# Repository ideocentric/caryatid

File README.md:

# caryatid

**A carrier board that gives a Daisy Seed a rechargeable battery, honest power
indication, and a fixed set of I/O on connectors, in a shape that drops into an
enclosure.**

Plenty of Seed carriers break out pins well. Fewer solve *running on a battery
you can charge without opening the box, and knowing what state that battery is
in when the instrument is switched off*. This board treats that as the core
requirement rather than an accessory.

**One PCB layout serves every build.** Every variable element (pots, keypad,
sensors, switches, comms) enters through a connector, and each instrument
populates the subset it needs. Order once, stuff per instrument. It carries
absonus, loa, baby borg, and whatever comes next.

### Is it right for what you are building?

**[docs/platform.md](docs/platform.md)** is the capability specification: what
it supports, what it deliberately does not, and where the boundary sits. It
states the limits as plainly as the features, because knowing them before you
commit is worth more than discovering them after.

### Status

**Five boards ordered 2026-08-23; none has been powered yet.**

Every electrical check is at zero: no unconnected nets, no shorts, no clearance
or hole violations, no copper under the width rule, no floating ground, and no
DRC violations of any kind. The firmware stub compiles against libDaisy and has
never been run on hardware. [docs/status.md](docs/status.md) is the current
state; treat anything marked unverified there as exactly that.

> **Working on caryatid itself rather than building with it?** Read
> [the checkout warning](#working-on-caryatid-itself) at the foot of this file
> before you commit anything. It is the one way to lose a session's work here.

## Start here

| | |
| --- | --- |
| **Where the board is, and what is next** | [docs/status.md](docs/status.md) |
| **The frozen pin map** | [docs/pinmap.md](docs/pinmap.md) — generated from [docs/pins.yaml](docs/pins.yaml) |
| Connectors and what plugs into them | [docs/connectors.md](docs/connectors.md) |
| Audio in and out, and the handset problem | [docs/audio.md](docs/audio.md) |
| **Setting the mic capsule jumpers** | [docs/mic-configurations.md](docs/mic-configurations.md) |
| The three indicators, and why three | [docs/indicators.md](docs/indicators.md) |
| **Component values, with derivations** | [docs/values.md](docs/values.md) |
| Part numbers, footprints, what is in stock | [docs/sourcing.md](docs/sourcing.md) |
| **Power sheet, every connection** | [docs/power-sheet.md](docs/power-sheet.md) |
| **Seed sheet, every connection** | [docs/seed-sheet.md](docs/seed-sheet.md) |
| **Panel I/O sheet, every connection** | [docs/panel-io-sheet.md](docs/panel-io-sheet.md) |
| **How to build an instrument on this board** | [docs/integration.md](docs/integration.md) |
| Board-support firmware (MIT) | [firmware/](firmware/) |
| What to do before and during capture | [docs/capture-checklist.md](docs/capture-checklist.md) |
| Datasheets, links and document numbers | [docs/datasheets.md](docs/datasheets.md) |
| **What it supports, and what it does not** | [docs/platform.md](docs/platform.md) |
| The board and schematic as PDFs | [docs/reference/](docs/reference/) |
| Why things are the way they are | [docs/decisions/](docs/decisions/) |
| **Rules the tools must follow, and what each cost** | [docs/conventions.md](docs/conventions.md) |

**`docs/pins.yaml` is the source of truth.** The markdown table is generated:

```sh
python3 tools/gen_pinmap.py           # rewrite docs/pinmap.md
python3 tools/gen_pinmap.py --check   # fail if stale
```

Never edit `pinmap.md` by hand. A pin map kept in two places will disagree the
first time a connector moves.

## Terms

**DNP — "do not populate."** The footprint is on the board, the symbol is in the
schematic, the connections exist in the netlist, but **no component is soldered
there**. A deliberately empty position. Also written DNI (do not install), NF
(not fitted), or NP.

**caryatid has none, and that is the point of the term appearing here.**
[ADR 0010](docs/decisions/0010-nothing-is-dnp.md) took the count to zero and
`check_board.py` check 12 keeps it there.

DNP used to be the mechanism this board rested on: lay out every option any of
the instruments might need, populate only the subset each build wants. It stopped
paying its way when JLCPCB began fitting the through-hole parts too — **DNP
became an instruction someone acts on and bills for**, so every DNP line is
either a part you paid for and did not want or one you needed and did not get,
and which it is only becomes clear when the boards arrive.

What replaced it is **selection after assembly**: six jumpers choose the mic
front-end per channel, and the codec's own PGA does the attenuating a resistor
pad used to. See [audio.md](docs/audio.md) and
[sourcing.md](docs/sourcing.md).

## What "frozen" means

An instrument may leave a pin unpopulated, and may choose between the alternates
listed for a pin. It may **not** repurpose one. The entire value of the platform
is that one layout serves every build; a pin reassigned for one instrument is a
board that no longer serves the others.

The map is **fully allocated**. `D30` is the only spare. Adding anything means
taking it from something else, and the decision records say what that would
cost.

## The fixed core

Populated on every build:

- Barrel jack → SS34 → **bq24074** charger with power path, ISET 890 Ω (1 A)
- **On-board 18650 holder (BT1)**, the only path to `VBAT` — a soldered holder
  cannot be wired backwards. Protected cell or protection PCB **required**
- **TPS61023** boost → **5.0 V** → ferrite + 100 µF → Seed VIN
- Illuminated latching power switch (3–9 V lamp, so `R_LED` is a 0 Ω link)
- `/CHG` + `/PGOOD` panel LEDs — the indication that works with the Seed off
- RGB status LED, battery gauge on A10, charge-status code on A11
- Daisy Seed on 2×(1×20) female headers, machine-fitted
- 74HC14 Schmitt debounce, SMT — see [ADR 0007](docs/decisions/0007-rc-and-schmitt-instead-of-the-ls18-p.md)
- Audio out; audio in on every board, **both channels**, capsule selected by
  jumper — JP1–JP3 left, JP4–JP6 right

## Two things worth knowing before you read the map

**Comms ports carry signals, not protocols.** D11/D12 are simultaneously I2C1
and UART4, so the same connector is an I2C sensor, a MIDI input, or an ESP32
bridge depending on what you plug in. Two ports is the ceiling — there is no
third UART on free pins. See [ADR 0003](docs/decisions/0003-comms-ports-are-protocol-agnostic.md).

**D8 is the only free SPI1 clock on the board.** Not a preference — `PA5` is the
only alternative and it is an analogue panel input. An earlier draft spent D8 on
an LED, which would have left SPI1 as two pins with nothing to clock them. See
[ADR 0004](docs/decisions/0004-keep-spi1-drop-the-soft-latch.md).

## Licence

**Settled 2026-08-18.** The hardware and the tools are strongly reciprocal; the
board-support layer deliberately is not:

| What | Licence |
| --- | --- |
| **Hardware** — schematics, PCB, footprints, artwork | **CERN-OHL-S v2** |
| **Tools** — everything in `tools/` | **GPL-3.0-or-later** |
| **Board support** — everything in `firmware/` | **MIT** |

Terms and what counts as *Complete Source* are in [LICENSING.md](LICENSING.md); how
it was reached, and the audit of every design input, are in
[ADR 0006](docs/decisions/0006-licensing-is-open.md).

CERN-OHL-S defines Complete Source as the **editable design files**, so shipping
Gerbers alone does not discharge the obligation. `CERN-OHL-S v2` and
`github.com/ideocentric/caryatid` are both printed on the front silkscreen.

The question this turned on — whether the schematic derived from Adafruit's
reference designs (CC BY-SA, and irreversible) or was drawn independently from
the TI datasheets — was answered **2026-08-08, before capture began**: drawn from
the datasheets. That is what kept the reciprocal option available.

**`firmware/` is MIT on purpose.** A copyleft board-support layer is viral into
anything that links it, which would settle every instrument's firmware licence
from underneath — a decision belonging to each instrument, not to the carrier
board. libDaisy and DaisySP are MIT already.

## Consuming this board

Each instrument takes it as a submodule:

```sh
git submodule add https://github.com/ideocentric/caryatid.git hardware/platform
```

loa consumes it this way at `hardware/platform`. Then add the board support to
your build:

```make
C_INCLUDES  += -Ihardware/platform/firmware/include
CPP_SOURCES += hardware/platform/firmware/src/caryatid.cpp
```

**Read [docs/integration.md](docs/integration.md) first** — it covers what the
board provides, what the instrument must provide, the electrical and mechanical
requirements, and the four things about this board that are not guessable from
a pin number.

## The name

*A caryatid is a column carved as a figure, bearing the weight of what stands on
it. Named for the role rather than for any instrument it carries: calling it
after one of them would have implied it belonged to that one.*

## Working on caryatid itself

### ⚠ Which checkout is this?

**caryatid is developed as a standalone clone. It is also consumed as a git
submodule by the instrument repositories, and those copies are read-only.**

If the path to this file runs through another project's submodule directory —
for loa that is `hardware/platform/` — **you are in a consumer copy. Do not edit
it and do not commit to it.** Find the standalone clone and work there.

The sequence, in order, every time:

1. Change, review and commit in the **standalone clone**.
2. Push.
3. *Then* update the consuming repository's submodule pointer — a
   `Bump caryatid: …` commit on that side.

**Why this matters more than it looks.** A submodule checkout sits on a detached
HEAD, so commits made there belong to no branch and the standalone clone knows
nothing about them. The two diverge silently, and the symptoms all point
somewhere other than the cause: KiCad in one directory keeps showing a schematic
that another directory has already changed.

That is not hypothetical. A whole session's work — ADR 0010, the schematic
edits, two tools, thirteen documents — was written into loa's submodule on
2026-08-21. It pushed to the same remote so nothing was lost, but an hour went
into diagnosing "update from schematic shows nothing new", which was only ever
the wrong directory.

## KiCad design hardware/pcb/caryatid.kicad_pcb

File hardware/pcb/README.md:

# PCB

KiCad 9 project. **All four sheets are captured.** 125 components, 101 nets,
**ERC clean at 0 violations.**

| Sheet | State | Check |
| --- | --- | --- |
| `power.kicad_sch` | 27 components, 19 nets | netlist diffed node-by-node against [power-sheet.md](../../docs/power-sheet.md); `ITERM` the one deliberate no-connect |
| `seed.kicad_sch` | 12 components | all **31** physical pins in `pins.yaml` land on a net named after the pin |
| `panel-io.kicad_sch` | 46 components | all **29** pins declaring a connector reach it, traversing series R and the debouncer |
| `audio.kicad_sch` | 37 placements, **0 DNP** | 17 nets diffed against [audio.md](../../docs/audio.md), including `C_g` in series with `R_g`; six jumpers re-diffed for [ADR 0010](../../docs/decisions/0010-nothing-is-dnp.md) |

**The dangling-global count reached zero.** It ran 33 → 4 → 0 as seed, panel-io
and audio landed, and each drop was predicted before the sheet was drawn. Five
no-connects remain and all five are deliberate: `ITERM` on the charger, `J11`
pin 9 (the spare), and the three unused 74HC14 outputs.

Treat any *new* ERC message as real. The design now has nothing expected to be
wrong, so there is no noise for a fault to hide in.

Placement is functional rather than tidy — components on a 1.27 mm grid with
labelled stubs, meant to be dragged into shape in the GUI. The bootstrap scripts
in [`tools/oneshot/`](../../tools/oneshot/) are spent; do not re-run them.

```
pcb/
  caryatid.kicad_pro       project: net classes, design rules, sheet index
  caryatid.kicad_sch       root — four hierarchical sheets, nothing else
  power.kicad_sch          charger, boost, latch, hardware charge LEDs
  seed.kicad_sch           Seed headers, battery gauge, charge-status code
  audio.kicad_sch          jacks, coupling, mic bias / preamp / pad options
  panel-io.kicad_sch       analogue bus, digital bus, switches, comms ports
  caryatid.kicad_sym       symbols: BQ24074RGT, TPS61023DRL, Seed sockets A/B
  caryatid.pretty/         footprints: BQ24074 QFN, Seed sockets A/B
  sym-lib-table            so the project libs resolve without global config
  fp-lib-table
```

Open `caryatid.kicad_pro`. `caryatid.kicad_pcb` carries **all 125 footprints,
placed and net-bound**, on a 150 × 90 mm outline with four M3 holes. **Nothing is
routed** — DRC's 263 unconnected items are the full ratsnest, which is correct.

Placement is a machine first pass, not layout. It puts each block where the
zoning says and nothing overhangs the outline, but ~33 courtyards still overlap
and the silkscreen is a mess. Treat it as something to drag from.

## Which face

**Everything is on the front.** The back carries nothing but the ground pour.

The SMD was briefly on the back, which is the textbook arrangement and was right
when the board was 90 × 100 and the copper under the cell was worth reclaiming.
It is wrong here: **the enclosure is shallow, so the standoff must be short**, and
C7 at 5.4 mm cannot hang underneath a 2 mm gap. Moving everything to the front
fixes three things at once — the standoff drops to 2 mm, SMT stays single-sided
and therefore Economic, and B.Cu is freed as a routing layer instead of carrying
104 parts *and* every signal.

The flip is stored the way KiCad stores it, checked against a KiCad-written
board rather than assumed: back-side footprints hold **Y-negated** coordinates,
F/B layer names swapped, and `(justify mirror)` on every text. Arcs survive
because KiCad 7+ stores start/mid/end and all three mirror together.

**Two things to confirm before ordering.**

`J13` is the SMD Qwiic socket, so it classified as SMD and went to the back.
Electrically fine; whether you want a Qwiic cable leaving from the underside is
a mechanical question, not one the classifier can answer.

**Through-hole bodies are on the front, so their pins protrude into the SMD
side.** JLC cannot wave-solder them from the back without hitting SMD. For small
runs their through-hole work is hand soldering, which is probably fine — but you
asked for the JSTs to be machine-fitted as on absonus, and absonus had a
component-free underside. Worth putting to JLC before the order.

## The connector ring

Placed by function, and stacked from measured courtyard extents rather than by
hand — hand arithmetic on offsets produced touching parts three times running.

| Edge | Connectors |
| --- | --- |
| Left | `J1` DC in, `J3` latch switch, `J4` charge LEDs |
| Left, inboard | `J11` digital bus IDC, beside A1 (the digital row) |
| Right | `J12` RGB, `J9` soft pot, `J10` FSR, `J17` audio out |
| Right, inboard | `J5` analogue bus IDC beside A2; `J16` expansion; `J18` audio in and `J14` mic return together |
| Bottom | `J6` `J7` `J8` switches, then `J19` and `J15` module ports |

Power enters on the left where the charger and boost sit underneath; the
analogue bus, both sensors and the audio pair are on the right, furthest from
L1. `J18` and `J14` are adjacent because they are one loom — capsule signal and
its bias return to the hook switch's second pole.

**Everything is at rotation 0.** A vertical JST exits upward, so turning the pin
row to follow the edge buys nothing — and the rotated-courtyard transform is the
one piece of geometry here that could not be checked against a known-good file,
so it is not used. If you rotate parts by hand in the GUI, KiCad does that
arithmetic correctly.

**The four M3 holes are part of the collision check.** They were not, at first,
and that version passed a board where `J6` and `J18` each sat on top of a
mounting hole. They come from the skeleton rather than from the netlist, which
is exactly why a check built around the component list missed them.

## Routing: the pour and the boost loop only

**Everything else is unrouted, deliberately.** kicad-cli has no router, KiCad
ships none, and Freerouting is not installed — and routing follows placement,
which is still a machine first pass. Two pieces were worth doing now because
their geometry is settled and the stakes are high.

**A GND zone on B.Cu**, which is now the empty face — a genuinely solid plane,
and the whole layer still available for routing around it.

**The zone is not filled.** `kicad-cli pcb drc` has no fill option, so DRC
reports the two GND vias as `via_dangling` — they touch a zone that has no copper
in it yet. **Fill zones in the board editor (`B`) and both clear.** That is a
tooling limit, not a fault.

**The boost hot loop.** `+5V_RAW` runs U2 pin 6 to C6 at 0.8 mm. The return is
deliberately **not a track**: C6's ground pad and U2's ground pad each drop a via
into the plane, so the return current runs directly beneath the outgoing current.
That is the smallest loop available and a track would be strictly worse.

Two things learned the hard way and worth keeping:

- **A track wider than the pad pitch shorts to the neighbouring pad.** 0.8 mm
  centred on U2 pin 6 overlapped pin 5. Every exit from a 0.5 mm-pitch pad now
  necks to 0.25 mm and widens once clear of the pad field.
- **Via positions are searched against every back-side pad**, not chosen by eye.
  The first attempt put a GND via straight through C7's `+5V` pad.

**`SW` is routed, and C6 moved to make it possible.** Putting the output cap
beside U2 was the obvious choice and it quietly cost the switching node: pin 5
can only exit right, and C6 was standing in that gap. C6 now sits **below** U2,
which frees the right side for L1 and — because pin 6 is on the near edge either
way — barely lengthens the hot loop.

| | beside | **below** |
| --- | --- | --- |
| Hot loop, pin 6 → C6 | 1.84 mm | 2.01 mm |
| SW node, pin 5 → L1 | 4.17 mm, **unroutable** | **2.31 mm at 1.2 mm wide** |

Trading 0.17 mm of hot loop for a routable 1.5 A switching node is not a close
call. The lesson is that *routability* is a placement constraint, and optimising
loop length without it produced an arrangement that measured well and could not
be built.

Three power pins leaving a 0.5 mm-pitch package share a 1.5 mm band, so every
exit necks to 0.2 mm and widens only once clear of the pad field. With that, the
routing adds **no** DRC violations of its own — the four clearance items are the
pre-existing SOT-563 pad-pitch ones.

## Routing the rest: Specctra DSN

`kicad-cli` has no router and no `dsn` export, so `tools/export_dsn.py` writes one:

```sh
python3 tools/export_dsn.py                 # -> hardware/pcb/caryatid.dsn
freerouting -de hardware/pcb/caryatid.dsn -do hardware/pcb/caryatid.ses
# KiCad: File > Import > Specctra Session
```

KiCad's own GUI export (File > Export > Specctra DSN) is more authoritative; this
exists so the export can be produced headlessly. The `.dsn` and `.ses` are
gitignored — regenerate rather than commit.

Two things it does that the GUI export does not:

- **GND is excluded from the routed nets.** F.Cu is a ground plane, which
  Freerouting cannot see, so it would otherwise scribble 72 ground traces across
  the board. GND wants stitching vias instead. `--with-gnd` overrides.
- **Existing copper is emitted `(type protect)`.** The boost hot loop and the SW
  node were placed and measured by hand; this stops the router discarding them.

**Not verified against Freerouting** — there is none on this machine. The file is
checked structurally (balanced, every padstack and net pin resolves, placements
inside the boundary) but has never been loaded by the tool it targets. Treat the
first import as the real test.

The conventions worth knowing if it ever needs debugging: coordinates are
millimetres × 10000, **DSN is Y-up so `dsn_y = -kicad_y`**, and images are the
canonical library footprint — unrotated and unmirrored — with side and rotation
carried in `(place ...)`. That last one matters because the board stores
back-side footprints already Y-negated, so using the placed copy would mirror
them twice.

## Silkscreen and clearance exceptions

**Back-side reference designators are hidden.** 104 SMD parts at this density
made them illegible and they collided 87 times; JLC places from the CPL file,
not from silkscreen. Front designators stay — that face is sparse and the
connectors are what a human cables up. Mounting holes carry no silk either.

**U1 and U2 have a footprint-level clearance override of 0.15 mm.** A 0.5 mm
pitch package fixes its own pad gaps — 0.25 mm on the QFN, 0.15 mm on the
SOT-563 — and the `HighCurrent` netclass asks 0.3 mm because `VBAT`, `VOUT` and
`VIN_DC` land on those pins. No land pattern at that pitch can meet it. The
exception is scoped to the two packages; every actual trace still answers to its
netclass.

Four violations survive that, and they are worth understanding rather than
silencing: `min_clearance` is a **board-wide floor of 0.2 mm that a local
override cannot go under**, and the SOT-563's own pads are 0.15 mm apart. To
clear them the board floor would have to drop to 0.15 — still comfortably above
JLC's 0.127 mm capability, since the netclasses would continue to govern
routing. That is a board-setup decision, not a footprint fix.

## How dense is it, really

| | mm² |
| --- | --- |
| All 125 courtyards | 4510 |
| of which BT1 | 1774 |
| everything except BT1 | **2736** |
| board | 13500 |
| face left after BT1 | 11726 |

**23% coverage on BT1's face** at 150 × 90 — comfortably inside the band for two
layers. It was 38% at the old 90 × 100. An earlier read of this said the board was "essentially
full"; that was wrong, and it was wrong for an instructive reason — the figure
came from a packer that added 1.6 mm around every part, which inflates an 0603
courtyard nearly six-fold. Measure coverage from courtyards, not from packing
margins.

What *is* tight is the connector ring. The edge connectors are 920 mm² of the
2736 and they all want board edge, which no rectangular zoning expresses. That
is the part worth doing by hand first.

Verified with `kicad-cli` rather than assumed: ERC runs clean and traverses all
four child sheets, and a netlist export resolves the full hierarchy.

```sh
KCLI=/Applications/KiCad/KiCad.app/Contents/MacOS/kicad-cli
"$KCLI" sch erc --output erc.rpt caryatid.kicad_sch
```

## Net classes

Set in the project file, with pattern assignment so nets land in the right class
as they are named rather than by hand afterwards.

| Class | Track | Clearance | Via | Applies to |
| --- | --- | --- | --- | --- |
| Default | 0.25 mm | 0.2 mm | 0.6 / 0.3 | everything else |
| Power | 0.8 mm | 0.25 mm | 0.8 / 0.4 | `+3V3`, `+3V3A`, `+5V` |
| HighCurrent | 1.2 mm | 0.3 mm | 1.0 / 0.5 | `VBAT`, `VOUT`, `VIN_DC`, `SW` |
| Analog | 0.3 mm | 0.25 mm | 0.6 / 0.3 | `A?`, `A??`, `AUDIO_*` |

`HighCurrent` is the one that matters. The cell delivers over an amp at low state
of charge and takes 1.29 A back while charging, and `SW` carries the boost's
switching current — 1.51 A peak at worst case. Those are not signal nets.

**Name the nets to match the patterns.** A net called `BAT+` will land in
Default and be routed at 0.25 mm, which is how a board gets warm.

**Local labels are sheet-qualified, and that defeats a bare pattern.** A power
symbol makes a global net called `VBAT`; a *local* label on the power sheet makes
a net called `/power/SW`. The pattern `SW` does not match `/power/SW`, so the
boost switching node — 1.51 A peak — would have silently fallen into Default.
The pattern is therefore `/power/SW`, spelled out. Any future HighCurrent or
Analog net carried on a local label needs the same treatment; global labels and
power symbols do not.

## Design rules

Set conservatively against JLCPCB's capabilities rather than at them: 0.2 mm
minimum track and clearance, 0.5 mm minimum via with a 0.3 mm hole. JLC will
accept finer, but a first spin is not the place to spend that margin.

**Two layers, 1.6 mm, 150 × 90 mm.** See
[ADR 0008](../../docs/decisions/0008-board-outline-and-layer-count.md). The old
"neither edge past 100 mm" rule is retired — it was a proxy for a price nobody
had checked, and checking it showed the increase is small. The 90 mm axis is
unchanged because it is the one proven against the BUD.

## Before capture

Work down [`../../docs/capture-checklist.md`](../../docs/capture-checklist.md).
The parts of it that gate everything else:

- **[ADR 0006](../../docs/decisions/0006-licensing-is-open.md) says draw from the
  TI datasheets.** No Adafruit schematic is opened during this work — deriving
  cannot be undone afterwards.
- **The pin map is frozen.** [`docs/pinmap.md`](../../docs/pinmap.md) is
  generated from `docs/pins.yaml`, and the schematic is a consumer of it, not a
  second opinion. Label Seed nets with pin names (`A7`, `D11`), not with what
  they happen to do on one instrument.
- **Three measurements still outstanding** — the handset capsule, the switch lamp
  current, and the mechanical parts that set panel standoff height. The first
  gates the audio sheet; the third gates any footprint placement.

Values are in [`docs/values.md`](../../docs/values.md), part numbers and
footprints in [`docs/sourcing.md`](../../docs/sourcing.md). Several absonus
footprints are reusable as-is, which turns a chunk of this into transcription.

## Footprints — checked against the stock libraries

Every footprint named in `sourcing.md` resolves in KiCad 9's stock libraries,
including the four JST XH ones that were assumed by naming convention rather
than verified. Two need a project-local variant, and both are already built.

**`caryatid:BQ24074RGT_QFN-16-1EP_3x3mm_P0.5mm`** — because **none** of the five
stock QFN-16 3×3 footprints put any paste on the exposed pad; every one is
`F.Cu`/`F.Mask` only. Derived from `EP1.7x1.7mm_ThermalVias` with a 2×2 aperture
array at 72% coverage. EP is 1.68 ±0.07 per SLUS810N drawing 4222419/E, so 1.7 is
inside tolerance.

**Thermal vias are 0.3 mm drill on 0.55 mm pads at ±0.5 mm.** TI's drawing calls
for Ø0.2 mm, which is below JLC's 0.3 mm minimum hole; and at TI's ±0.6 position
a 0.55 mm pad leaves only 0.176 mm to the signal pads. Moving them inboard to
±0.5 gives 0.289 mm and satisfies both.

**The exposed pad is 1.68 mm, TI's nominal.** It was briefly 1.70 — inherited
from the stock footprint that had a ThermalVias sibling — which lands *exactly*
on the 0.2 mm clearance boundary and fails on rounding.

Two caveats worth carrying into layout and into the order:

- **The four thermal vias sit under the paste apertures and must be tented.** On
  a 1.68 mm pad the vias and the apertures both want the corners; making them
  disjoint drops coverage to 45%. This is a via setting, not a footprint fix.
- The only package drawing in the datasheet is **RGT0016C**, while Table 7-1
  lists the '74 as **RGT0016B**. TI did not publish the B drawing. If the two
  differ, the EP dimension is what changes.

**`caryatid:DaisySeed_Socket_A_1x20` / `_B_1x20`** — two 1×20 socket rows so the
BOM asks for two sockets from the schematic. They carry the module outline,
pin-1 dot, square pads at the USB end of both rows and the `USB` legend, split on
the centreline so wrong spacing shows as a broken outline. Per-pin labels were
drawn and dropped — see [`docs/seed-sheet.md`](../../docs/seed-sheet.md).

## Silkscreen: JLCPCB's numbers

| | Absolute minimum | Recommended |
| --- | --- | --- |
| Character height | **0.8 mm** | ≥ 1.0 mm |
| Line width | **0.15 mm** | ≥ 0.2 mm |
| Pad-to-silk clearance | — | ≥ 0.25 mm |

Two project rules were looser than that and have been tightened:
`min_text_thickness` 0.08 → **0.15**, and `min_silk_clearance` 0 → **0.25**,
which was disabled entirely. `min_text_height` was already correct at 0.8.

Expect the silk-overlap count to *rise* after that change. It is not a
regression — the rule was previously not checking.

**BT1 is settled and needs no project-local work**: MPD `BH-18650-PC`,
`C5339083`, on stock `Battery:BatteryHolder_MPD_BH-18650-PC`, whose pads match
the drawing exactly (72.90 mm terminals, 55.61 mm mounting holes). It is rated
for protected cells, which was the open question. The Keystone 1042 was rejected
— 87.9 mm of courtyard against the MPD's 79.2 mm.

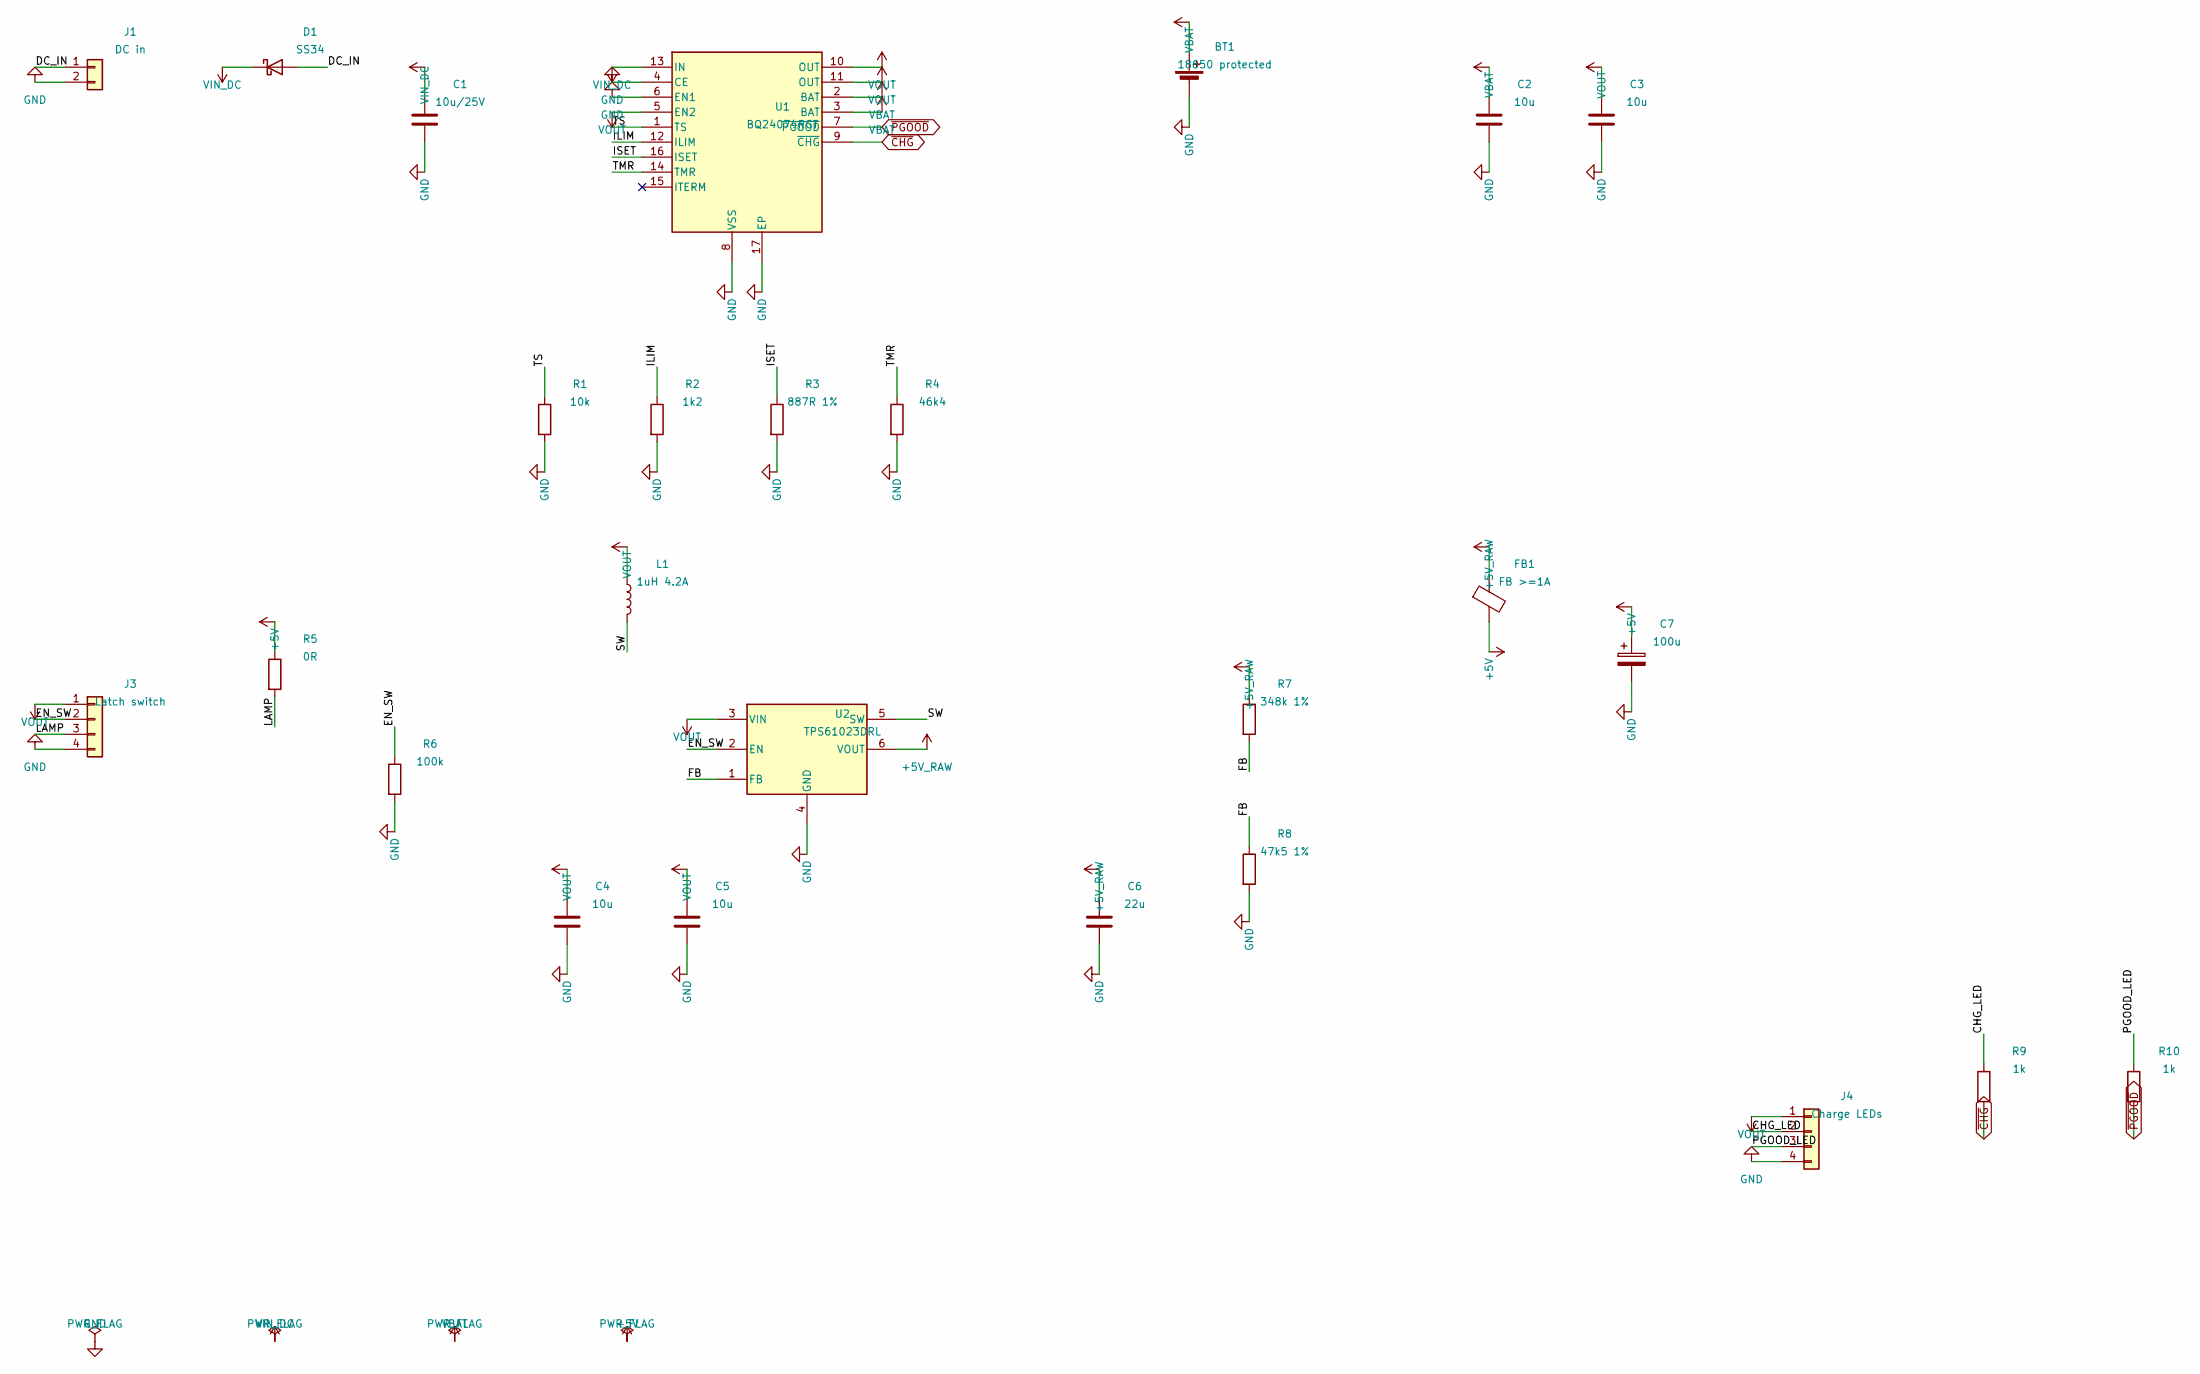
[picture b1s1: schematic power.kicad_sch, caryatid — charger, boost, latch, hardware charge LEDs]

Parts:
BT1: 18650 protected; BatteryHolder_MPD_BH-18650-PC
C1: 10u/25V; C_0805_2012Metric
C2, C3, C4, C5: 10u; C_0805_2012Metric
C6: 22u; C_0805_2012Metric
C7: 100u; CP_Elec_6.3x5.4
D1: SS34; D_SMA
FB1: FB >=1A; L_0805_2012Metric
J1: DC in; JST_XH_B2B-XH-A_1x02_P2.50mm_Vertical
J3: Latch switch; JST_XH_B4B-XH-A_1x04_P2.50mm_Vertical
J4: Charge LEDs; JST_XH_B4B-XH-A_1x04_P2.50mm_Vertical
L1: 1uH 4.2A; L_Vishay_IFSC-1515AH_4x4x1.8mm
R1: 10k; R_0603_1608Metric
R2: 1k2; R_0603_1608Metric
R3: 887R 1%; R_0603_1608Metric
R4: 46k4; R_0603_1608Metric
R5: 0R; R_0603_1608Metric
R6: 100k; R_0603_1608Metric
R7: 348k 1%; R_0603_1608Metric
R8: 47k5 1%; R_0603_1608Metric
R9, R10: 1k; R_0603_1608Metric
U1: BQ24074RGT; BQ24074RGT_QFN-16-1EP_3x3mm_P0.5mm
U2: TPS61023DRL; SOT-563

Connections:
+5V: C7.1, FB1.2, R5.1; also elsewhere on the board
+5V_RAW: C6.1, FB1.1, R7.1, U2.6 (VOUT)
/power/CHG_LED: J4.2, R9.1
/power/DC_IN: D1.2 (A), J1.1
/power/EN_SW: J3.2, R6.1, U2.2 (EN)
/power/FB: R7.2, R8.1, U2.1 (FB)
/power/ILIM: R2.1, U1.12 (ILIM)
/power/ISET: R3.1, U1.16 (ISET)
/power/LAMP: J3.3, R5.2
/power/PGOOD_LED: J4.3, R10.1
/power/SW: L1.2, U2.5 (SW)
/power/TMR: R4.1, U1.14 (TMR)
/power/TS: R1.1, U1.1 (TS)
GND: BT1.2 (-), C1.2, C2.2, C3.2, C4.2, C5.2, C6.2, C7.2, J1.2, J3.4, J4.4, R1.2, R2.2, R3.2, R4.2, R6.2, R8.2, U1.4 (CE), U1.6 (EN1), U1.8 (VSS), U1.17 (EP), U2.4 (GND); also elsewhere on the board
VBAT: BT1.1 (+), C2.1, U1.2 (BAT), U1.3 (BAT); also elsewhere on the board
VIN_DC: C1.1, D1.1 (K), U1.13 (IN)
VOUT: C3.1, C4.1, C5.1, J3.1, J4.1, L1.1, U1.5 (EN2), U1.10 (OUT), U1.11 (OUT), U2.3 (VIN)
~CHG: R9.2, U1.9 (~CHG); also elsewhere on the board
~PGOOD: R10.2, U1.7 (~PGOOD); also elsewhere on the board

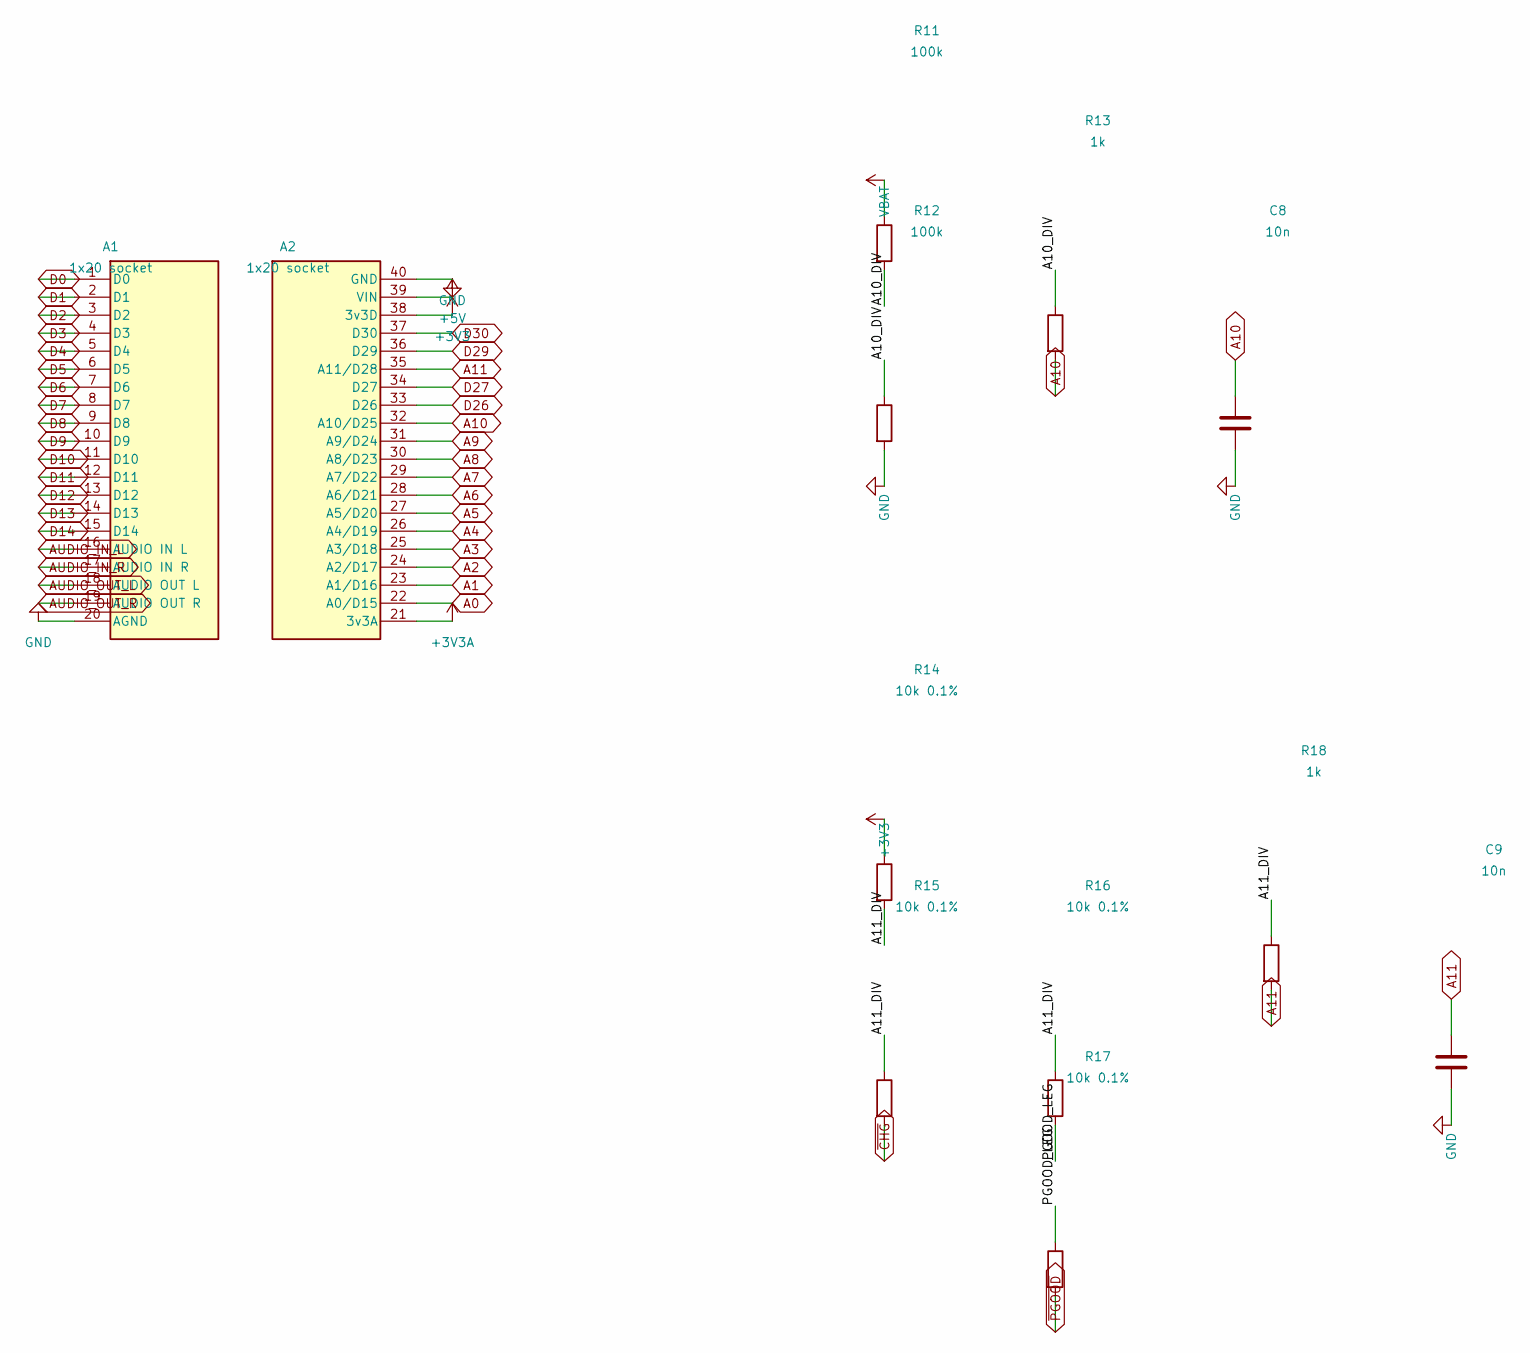
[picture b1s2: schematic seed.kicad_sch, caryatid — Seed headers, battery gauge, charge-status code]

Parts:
A1: 1x20 socket; DaisySeed_Socket_A_1x20
A2: 1x20 socket; DaisySeed_Socket_B_1x20
C8, C9: 10n; C_0603_1608Metric
R11, R12: 100k; R_0603_1608Metric
R13, R18: 1k; R_0603_1608Metric
R14, R15, R16, R17: 10k 0.1%; R_0603_1608Metric

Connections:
+3V3: A2.38 (3v3D), R14.1; also elsewhere on the board
+3V3A: A2.21 (3v3A); also elsewhere on the board
+5V: A2.39 (VIN); also elsewhere on the board
/seed/A10_DIV: R11.2, R12.1, R13.1
/seed/A11_DIV: R14.2, R15.1, R16.1, R18.1
/seed/PGOOD_LEG: R16.2, R17.1
A0: A2.22 (A0/D15); also elsewhere on the board
A1: A2.23 (A1/D16); also elsewhere on the board
A2: A2.24 (A2/D17); also elsewhere on the board
A3: A2.25 (A3/D18); also elsewhere on the board
A4: A2.26 (A4/D19); also elsewhere on the board
A5: A2.27 (A5/D20); also elsewhere on the board
A6: A2.28 (A6/D21); also elsewhere on the board
A7: A2.29 (A7/D22); also elsewhere on the board
A8: A2.30 (A8/D23); also elsewhere on the board
A9: A2.31 (A9/D24); also elsewhere on the board
A10: A2.32 (A10/D25), C8.1, R13.2
A11: A2.35 (A11/D28), C9.1, R18.2
AUDIO_IN_L: A1.16 (AUDIO_IN_L); also elsewhere on the board
AUDIO_IN_R: A1.17 (AUDIO_IN_R); also elsewhere on the board
AUDIO_OUT_L: A1.18 (AUDIO_OUT_L); also elsewhere on the board
AUDIO_OUT_R: A1.19 (AUDIO_OUT_R); also elsewhere on the board
D0: A1.1 (D0); also elsewhere on the board
D1: A1.2 (D1); also elsewhere on the board
D2: A1.3 (D2); also elsewhere on the board
D3: A1.4 (D3); also elsewhere on the board
D4: A1.5 (D4); also elsewhere on the board
D5: A1.6 (D5); also elsewhere on the board
D6: A1.7 (D6); also elsewhere on the board
D7: A1.8 (D7); also elsewhere on the board
D8: A1.9 (D8); also elsewhere on the board
D9: A1.10 (D9); also elsewhere on the board
D10: A1.11 (D10); also elsewhere on the board
D11: A1.12 (D11); also elsewhere on the board
D12: A1.13 (D12); also elsewhere on the board
D13: A1.14 (D13); also elsewhere on the board
D14: A1.15 (D14); also elsewhere on the board
D26: A2.33 (D26); also elsewhere on the board
D27: A2.34 (D27); also elsewhere on the board
D29: A2.36 (D29); also elsewhere on the board
D30: A2.37 (D30); also elsewhere on the board
GND: A1.20 (AGND), A2.40 (GND), C8.2, C9.2, R12.2; also elsewhere on the board
VBAT: R11.1; also elsewhere on the board
~CHG: R15.2; also elsewhere on the board
~PGOOD: R17.2; also elsewhere on the board

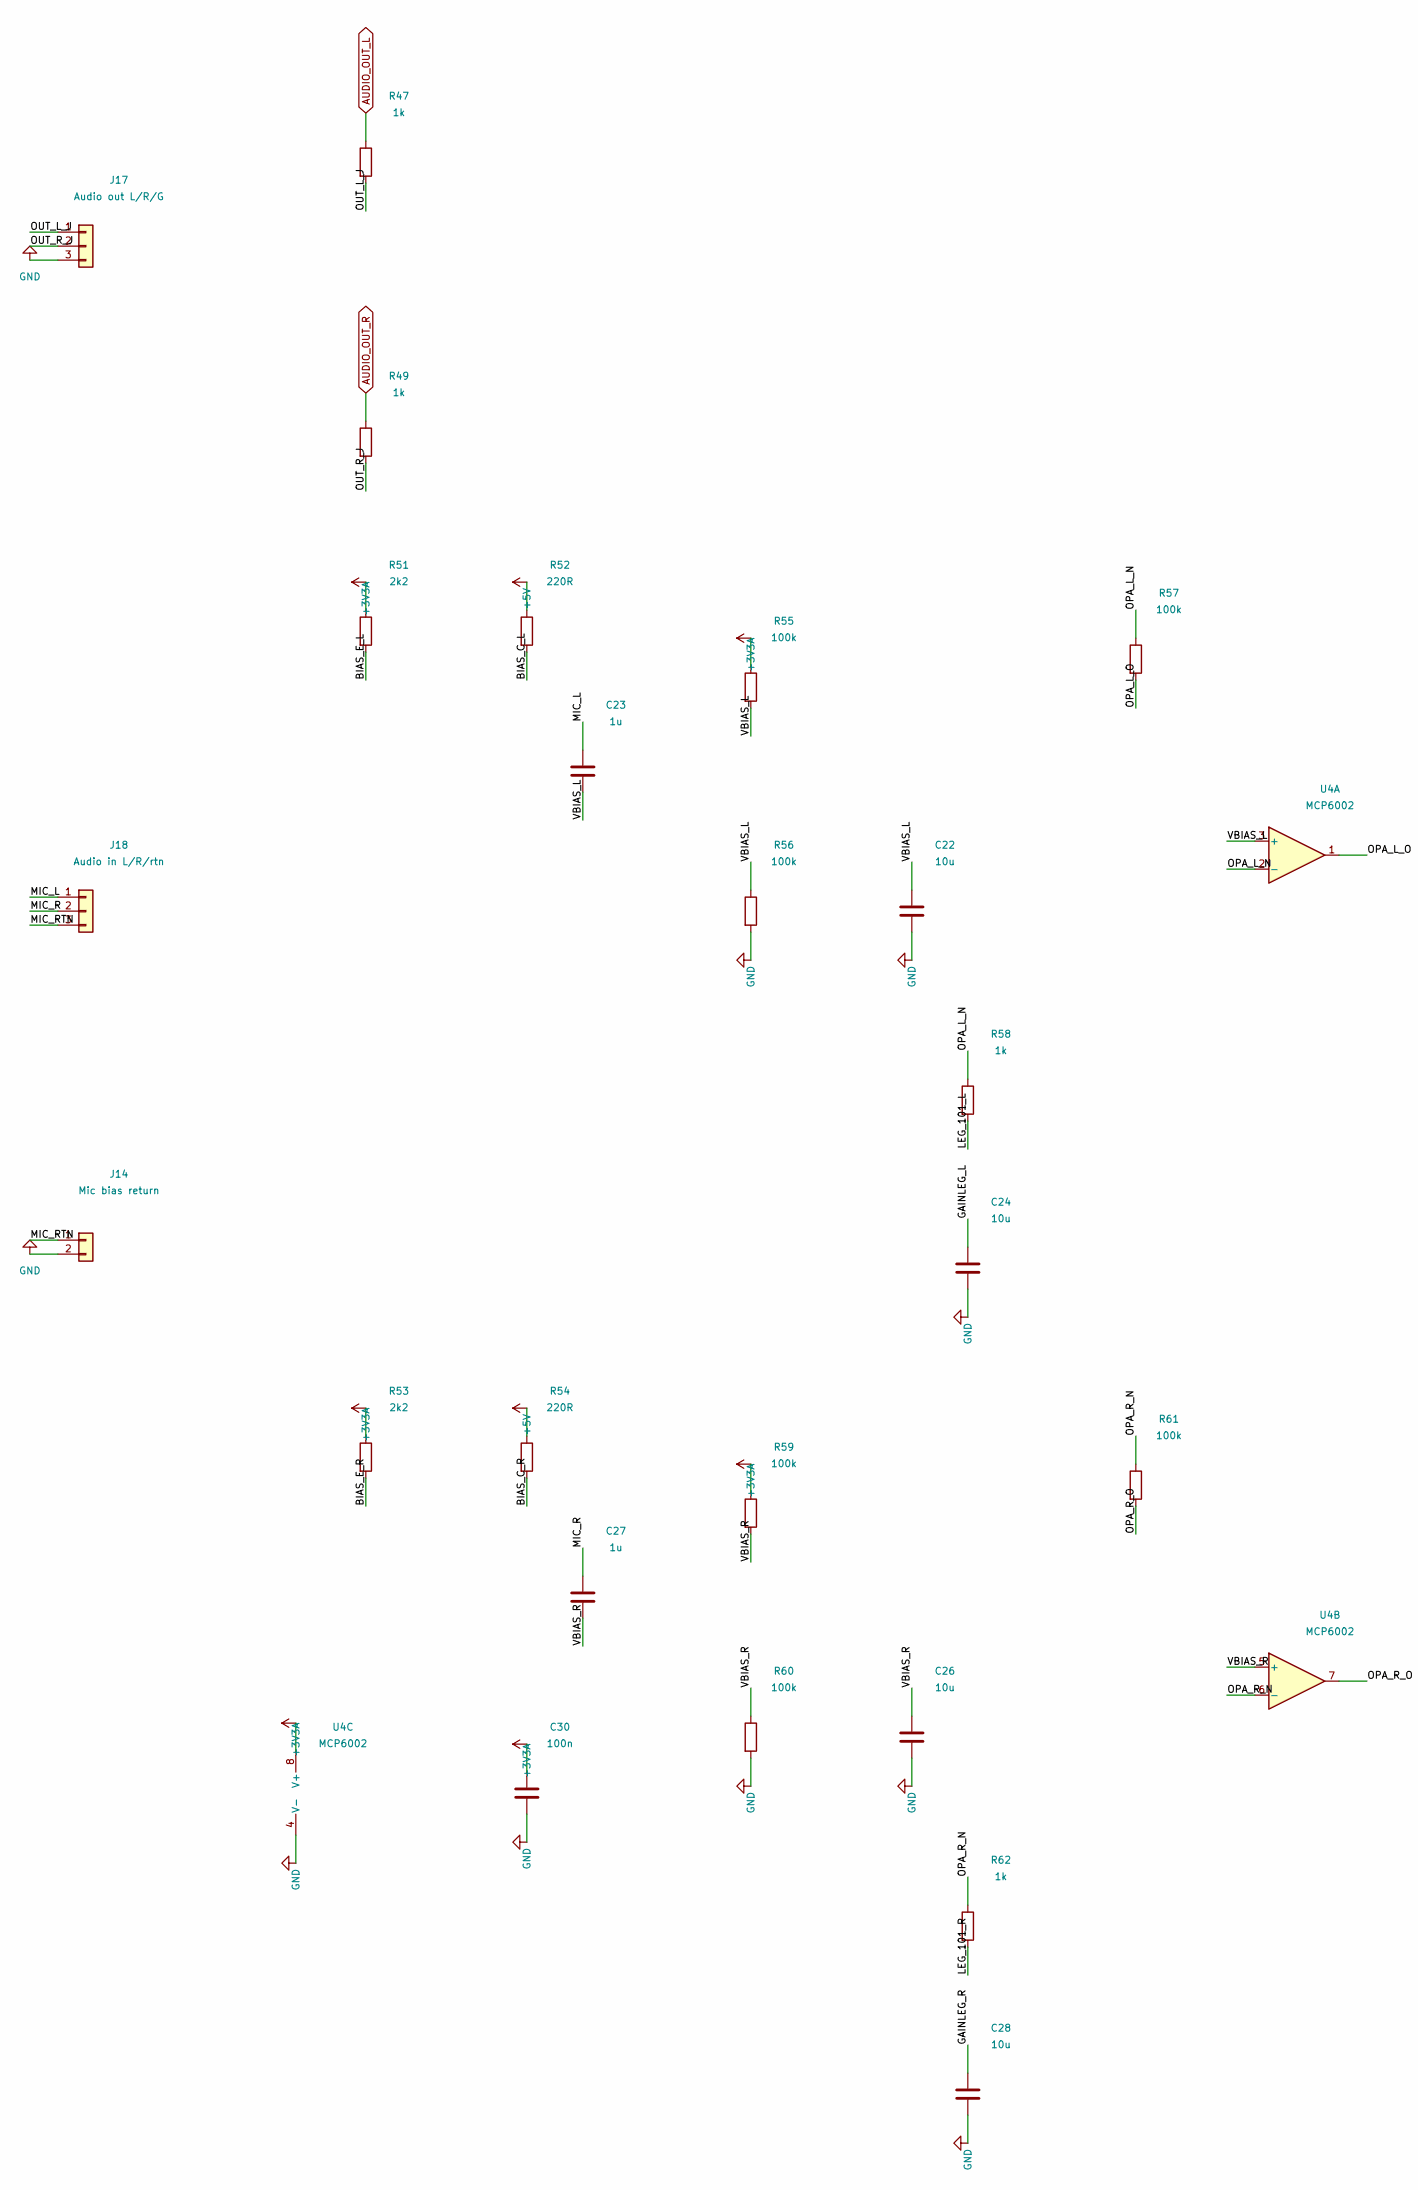
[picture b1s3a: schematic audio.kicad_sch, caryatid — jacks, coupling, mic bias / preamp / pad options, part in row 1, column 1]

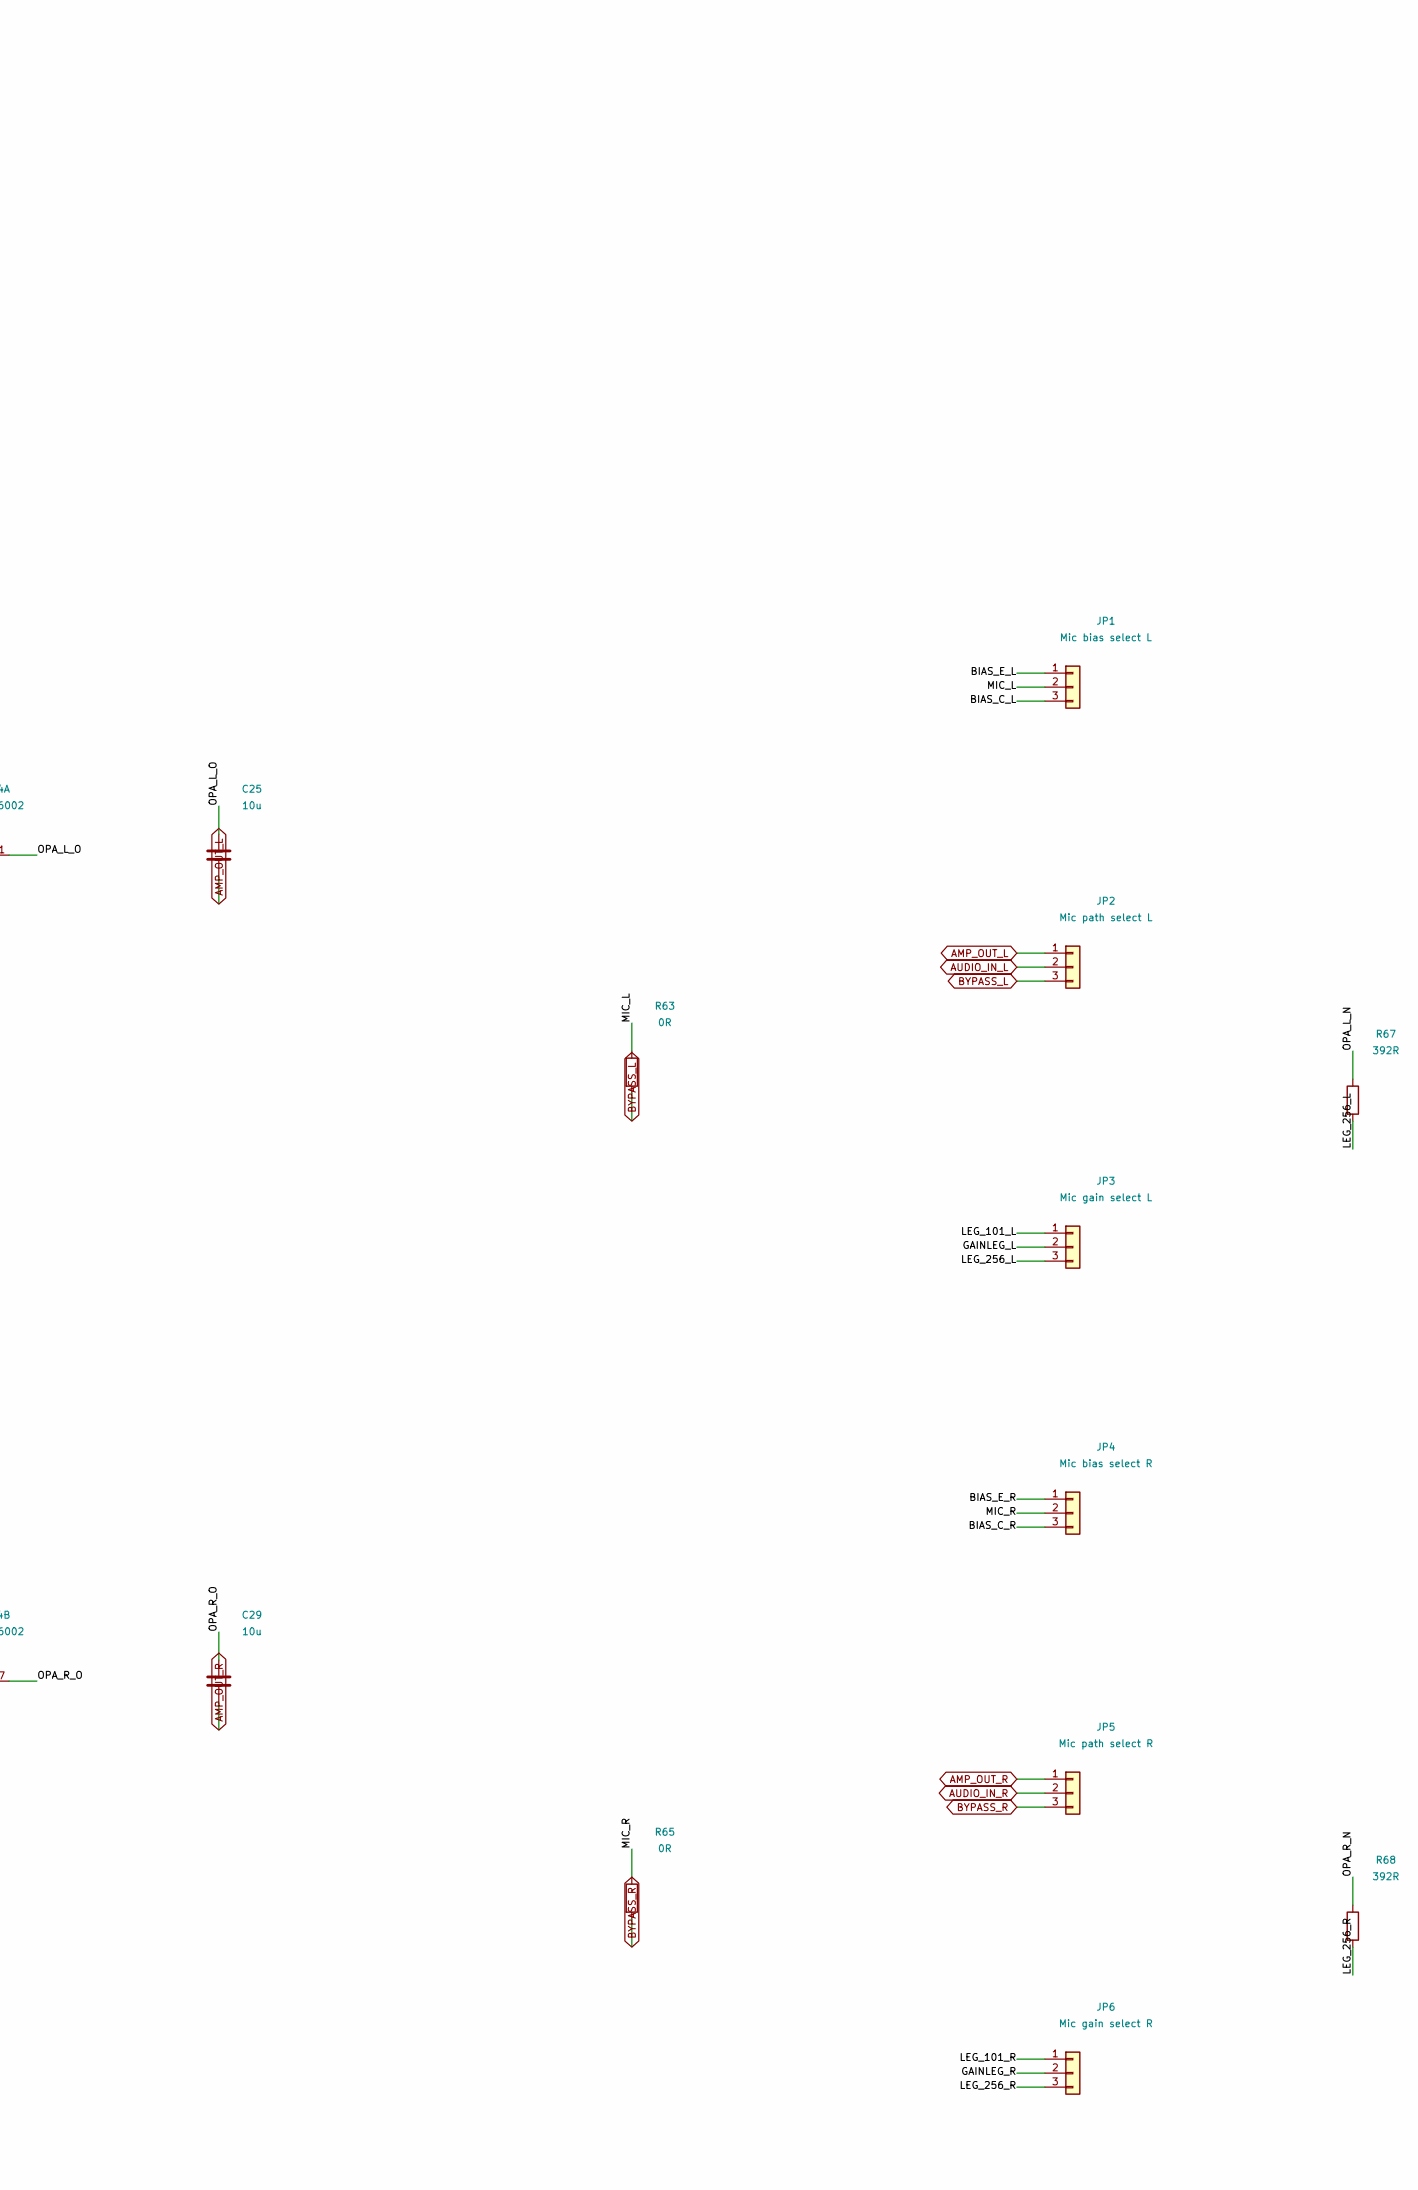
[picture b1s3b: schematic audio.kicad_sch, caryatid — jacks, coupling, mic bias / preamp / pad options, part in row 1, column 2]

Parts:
C22, C24, C25, C26, C28, C29: 10u; C_0805_2012Metric
C23, C27: 1u; C_0603_1608Metric
C30: 100n; C_0603_1608Metric
J14: Mic bias return; JST_XH_B2B-XH-A_1x02_P2.50mm_Vertical
J17: Audio out L/R/G; JST_XH_B3B-XH-A_1x03_P2.50mm_Vertical
J18: Audio in L/R/rtn; JST_XH_B3B-XH-A_1x03_P2.50mm_Vertical
JP1: Mic bias select L; PinHeader_1x03_P2.54mm_Vertical
JP2: Mic path select L; PinHeader_1x03_P2.54mm_Vertical
JP3: Mic gain select L; PinHeader_1x03_P2.54mm_Vertical
JP4: Mic bias select R; PinHeader_1x03_P2.54mm_Vertical
JP5: Mic path select R; PinHeader_1x03_P2.54mm_Vertical
JP6: Mic gain select R; PinHeader_1x03_P2.54mm_Vertical
R47, R49, R58, R62: 1k; R_0603_1608Metric
R51, R53: 2k2; R_0603_1608Metric
R52, R54: 220R; R_0603_1608Metric
R55, R56, R57, R59, R60, R61: 100k; R_0603_1608Metric
R63, R65: 0R; R_0603_1608Metric
R67, R68: 392R; R_0603_1608Metric
U4: MCP6002; SOIC-8_3.9x4.9mm_P1.27mm

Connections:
+3V3A: C30.1, R51.1, R53.1, R55.1, R59.1, U4.8 (V+); also elsewhere on the board
+5V: R52.1, R54.1; also elsewhere on the board
/audio/BIAS_C_L: JP1.3, R52.2
/audio/BIAS_C_R: JP4.3, R54.2
/audio/BIAS_E_L: JP1.1, R51.2
/audio/BIAS_E_R: JP4.1, R53.2
/audio/GAINLEG_L: C24.1, JP3.2
/audio/GAINLEG_R: C28.1, JP6.2
/audio/LEG_101_L: JP3.1, R58.2
/audio/LEG_101_R: JP6.1, R62.2
/audio/LEG_256_L: JP3.3, R67.2
/audio/LEG_256_R: JP6.3, R68.2
/audio/MIC_L: C23.1, J18.1, JP1.2, R63.1
/audio/MIC_R: C27.1, J18.2, JP4.2, R65.1
/audio/MIC_RTN: J14.1, J18.3
/audio/OPA_L_N: R57.1, R58.1, R67.1, U4.2 (-)
/audio/OPA_L_O: C25.1, R57.2, U4.1
/audio/OPA_R_N: R61.1, R62.1, R68.1, U4.6 (-)
/audio/OPA_R_O: C29.1, R61.2, U4.7
/audio/OUT_L_J: J17.1, R47.2
/audio/OUT_R_J: J17.2, R49.2
/audio/VBIAS_L: C22.1, C23.2, R55.2, R56.1, U4.3 (+)
/audio/VBIAS_R: C26.1, C27.2, R59.2, R60.1, U4.5 (+)
AMP_OUT_L: C25.2, JP2.1
AMP_OUT_R: C29.2, JP5.1
AUDIO_IN_L: JP2.2; also elsewhere on the board
AUDIO_IN_R: JP5.2; also elsewhere on the board
AUDIO_OUT_L: R47.1; also elsewhere on the board
AUDIO_OUT_R: R49.1; also elsewhere on the board
BYPASS_L: JP2.3, R63.2
BYPASS_R: JP5.3, R65.2
GND: C22.2, C24.2, C26.2, C28.2, C30.2, J14.2, J17.3, R56.2, R60.2, U4.4 (V-); also elsewhere on the board
